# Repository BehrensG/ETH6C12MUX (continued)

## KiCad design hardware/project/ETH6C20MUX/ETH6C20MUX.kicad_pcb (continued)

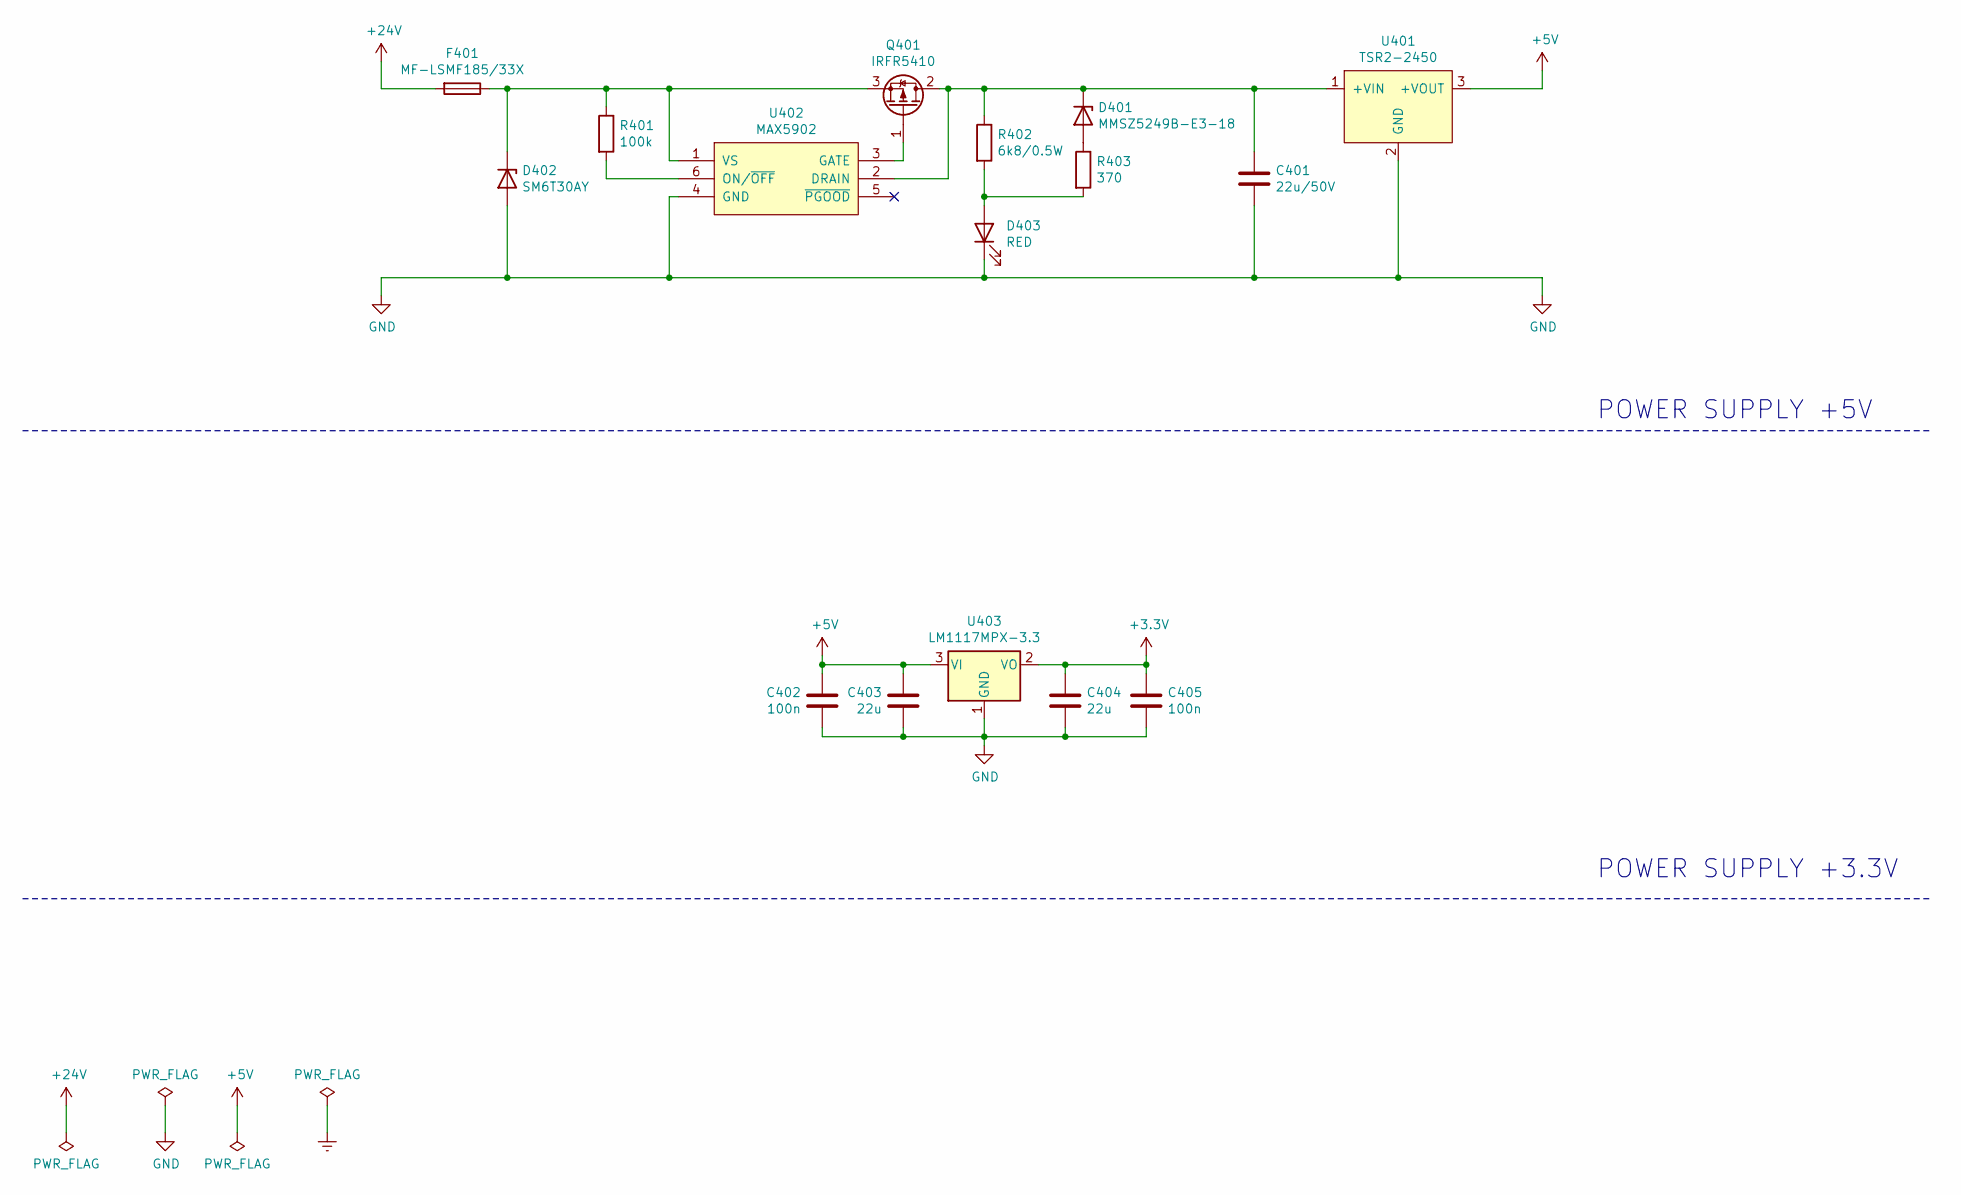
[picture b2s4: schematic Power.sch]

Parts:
C401: 22u/50V; C_2220_5650Metric_Pad1.97x5.40mm_HandSolder
C402, C405: 100n; C_0603_1608Metric_Pad1.08x0.95mm_HandSolder
C403, C404: 22u; C_1210_3225Metric_Pad1.42x2.65mm_HandSolder
D401: MMSZ5249B-E3-18; D_SOD-123
D402: SM6T30AY; DO_214AA_REV
D403: RED; LED_0603_1608Metric_Pad1.05x0.95mm_HandSolder
F401: MF-LSMF185/33X; Fuse_SMD2920
Q401: IRFR5410; TO-252-2_Rectifier
R401: 100k; R_0603_1608Metric_Pad0.98x0.95mm_HandSolder
R402: 6k8/0.5W; R_0603_1608Metric_Pad0.98x0.95mm_HandSolder
R403: 370; R_0603_1608Metric_Pad0.98x0.95mm_HandSolder
U401: TSR2-2450; TSR2
U402: MAX5902; SOT-23-6_Handsoldering
U403: LM1117MPX-3.3; SOT-223-3_TabPin2

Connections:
+3V3: C404.1, C405.1, U403.2 (VO); also elsewhere on the board
+5V: C402.1, C403.1, U401.3 (+VOUT), U403.3 (VI); also elsewhere on the board
+24V: F401.2; also elsewhere on the board
GND: C401.2, C402.2, C403.2, C404.2, C405.2, D402.2 (A), D403.1 (K), U401.2 (GND), U402.4 (GND), U403.1 (GND); also elsewhere on the board
unnamed: C401.1, D401.1 (K), Q401.2 (D), R402.1, U401.1 (+VIN), U402.2 (DRAIN)
unnamed: D401.2 (A), R403.1
unnamed: D402.1 (K), F401.1, Q401.3 (S), R401.1, U402.1 (VS)
unnamed: D403.2 (A), R402.2, R403.2
unnamed: Q401.1 (G), U402.3 (GATE)
unnamed: R401.2, U402.6 (ON/~OFF)

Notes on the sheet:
POWER SUPPLY +5V
POWER SUPPLY +3.3V

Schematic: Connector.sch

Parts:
F501, F502, F503, F504, F505, F506: 0470001.DRSNP; 0470
J501: Conn_01x06; PinSocket_1x06_P2.54mm_Vertical
J502: Conn_02x08_Odd_Even; PinSocket_2x08_P2.54mm_Vertical
J503: C64AC; Socket_DIN41612-CaseC1-AC-Male-64Pin-2rows

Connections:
+5V: J502.2, J502.4; also elsewhere on the board
+24V: J503.A31 (31A), J503.A32 (32A), J503.C31 (31C), J503.C32 (32C); also elsewhere on the board
/Connector/A: F501.2, J501.1, J501.2; also elsewhere on the board
/Connector/B: F502.2, J501.3, J501.4; also elsewhere on the board
/Connector/C: F503.2, J501.5, J501.6; also elsewhere on the board
/Connector/D: F504.2, J501.11, J501.12; also elsewhere on the board
/Connector/E: F505.2, J501.9, J501.10; also elsewhere on the board
/Connector/F: F506.2, J501.7, J501.8; also elsewhere on the board
/Connector/MODULE_DETECT0: J502.12; also elsewhere on the board
/Connector/MODULE_DETECT1: J502.14; also elsewhere on the board
/Connector/RELAY2_SCLK: J502.1; also elsewhere on the board
/Connector/RELAY2_SI: J502.5; also elsewhere on the board
/Connector/RELAY2_SO: J502.3; also elsewhere on the board
/Connector/RELAY2_~CS0: J502.9; also elsewhere on the board
/Connector/RELAY2_~CS1: J502.11; also elsewhere on the board
/Connector/RELAY2_~CS2: J502.13; also elsewhere on the board
/Connector/RELAY2_~CS3: J502.15; also elsewhere on the board
/Connector/RELAY2_~CS4: J502.16; also elsewhere on the board
/Connector/RELAY2_~RST: J502.7; also elsewhere on the board
/Connector/RX+: J503.A20 (20A); also elsewhere on the board
/Connector/RX-: J503.A21 (21A); also elsewhere on the board
/Connector/TX+: J503.C20 (20C); also elsewhere on the board
/Connector/TX-: J503.C21 (21C); also elsewhere on the board
Earth: J503.A18 (18A), J503.A22 (22A), J503.C18 (18C), J503.C22 (22C); also elsewhere on the board
GND: J502.6, J502.8, J503.A27 (27A), J503.A28 (28A), J503.C27 (27C), J503.C28 (28C); also elsewhere on the board
unnamed: F501.1, J503.A2 (2A), J503.C2 (2C)
unnamed: F502.1, J503.A3 (3A), J503.C3 (3C)
unnamed: F503.1, J503.A4 (4A), J503.C4 (4C)
unnamed: F504.1, J503.A5 (5A), J503.C5 (5C)
unnamed: F505.1, J503.A6 (6A), J503.C6 (6C)
unnamed: F506.1, J503.A7 (7A), J503.C7 (7C)

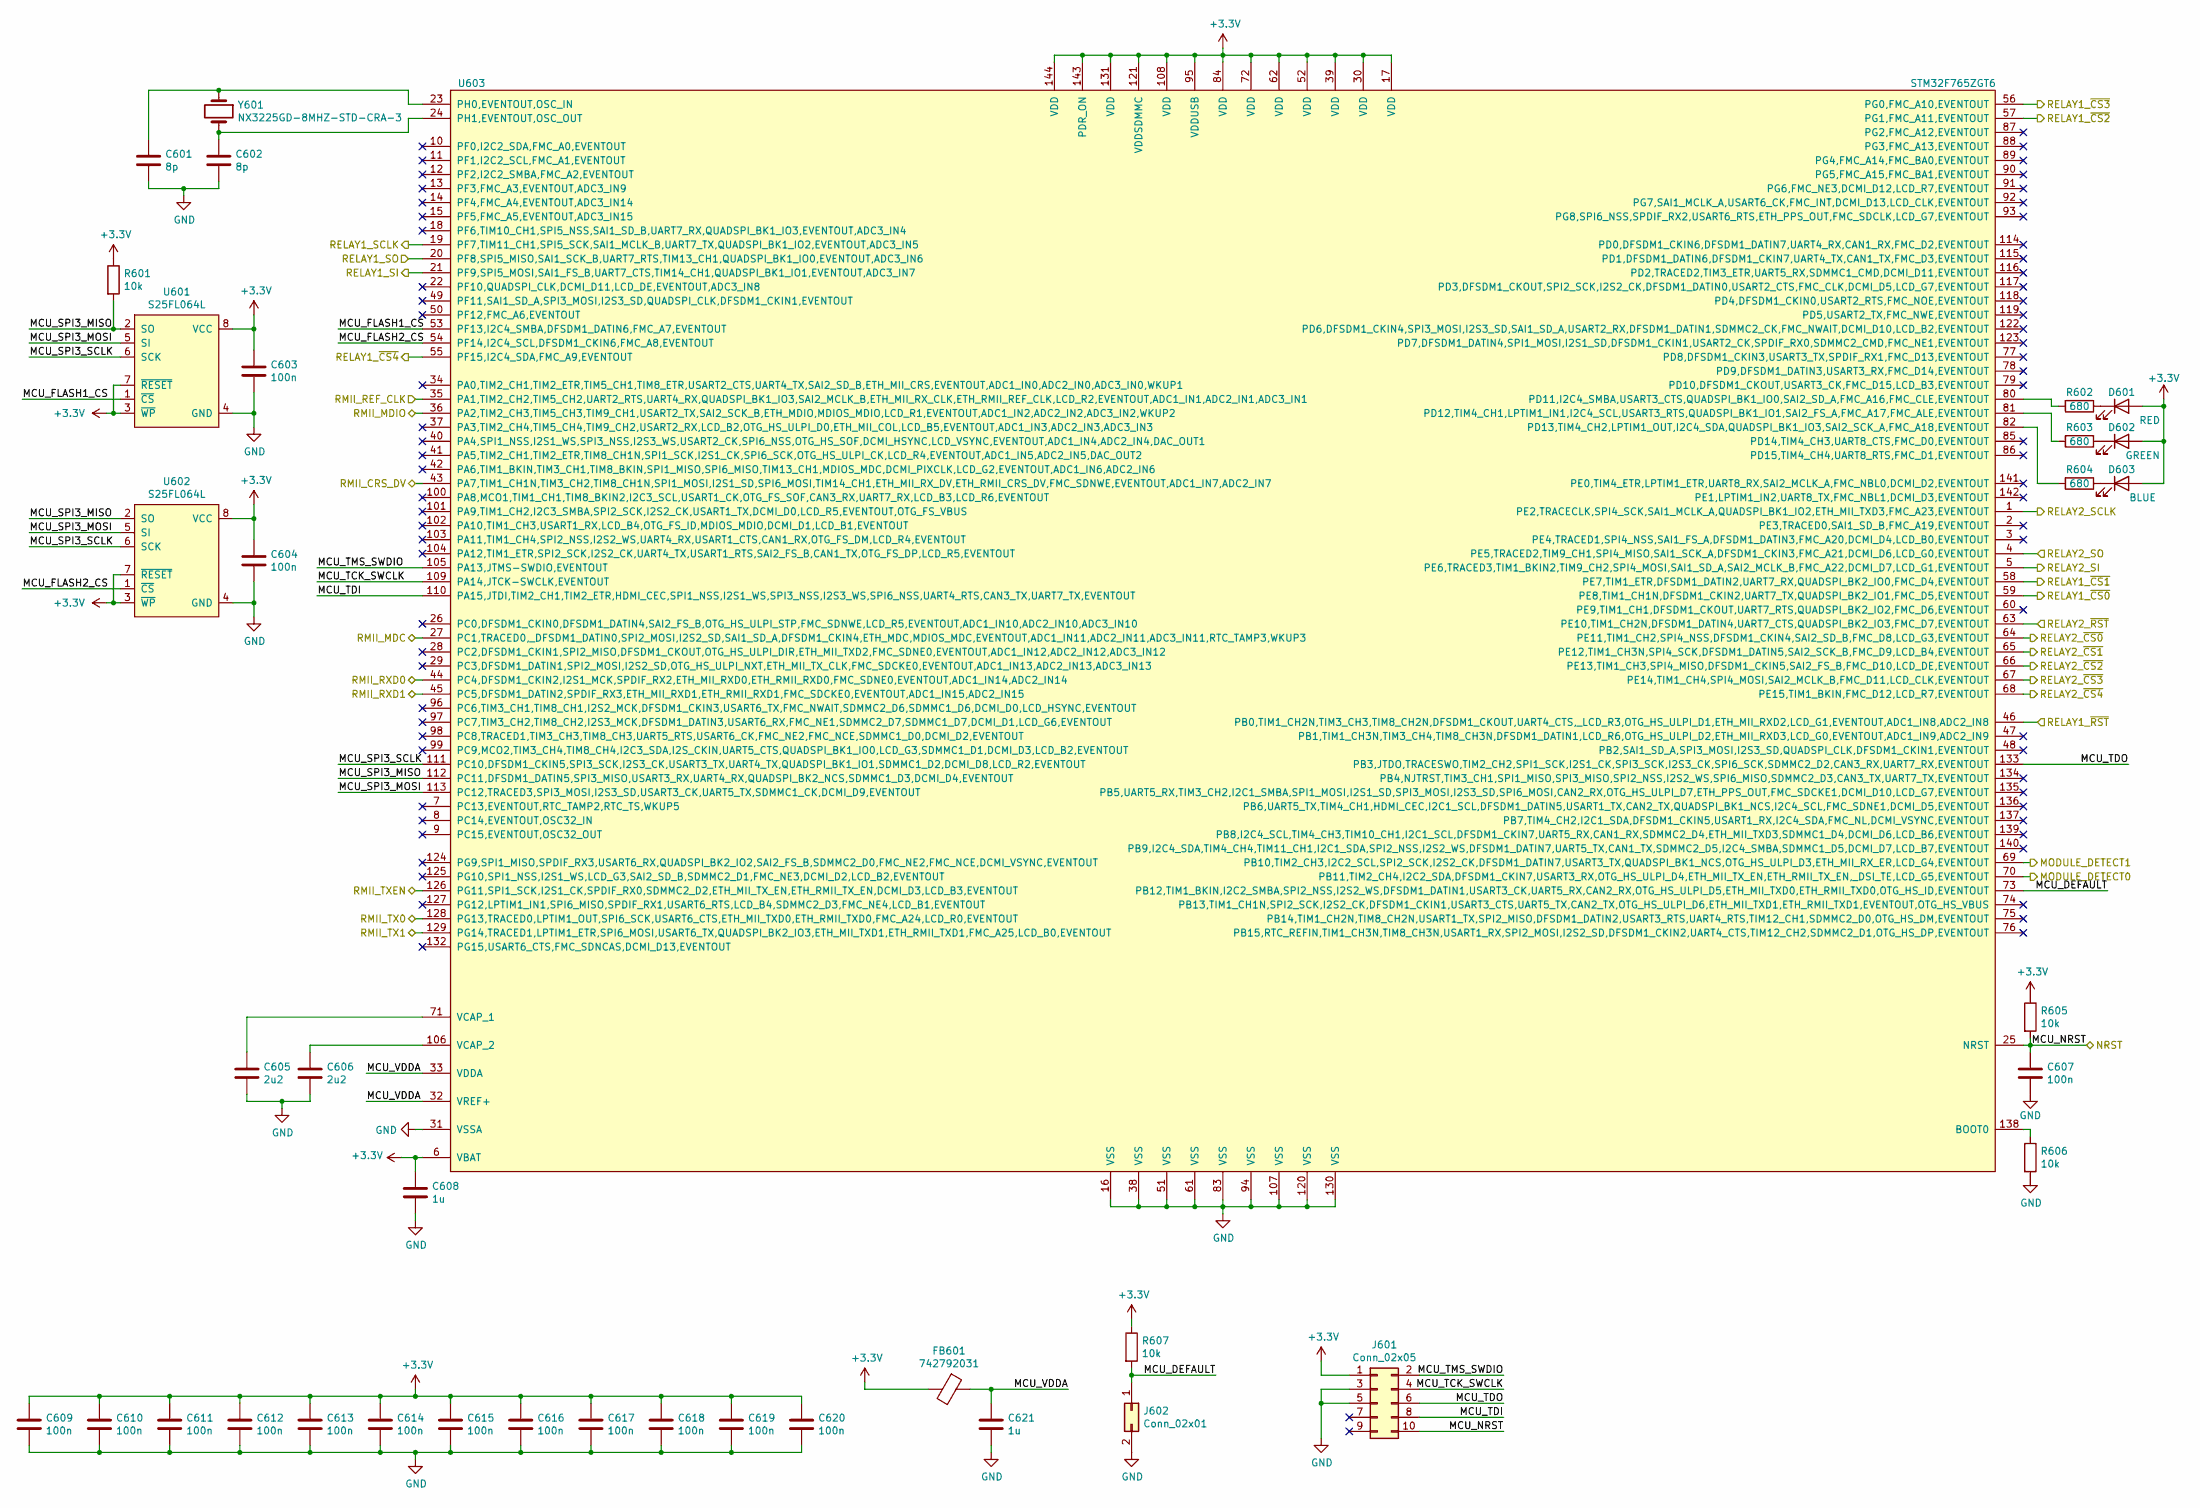
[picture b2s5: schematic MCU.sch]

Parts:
C601, C602: 8p; C_0603_1608Metric_Pad1.08x0.95mm_HandSolder
C603, C604, C607, C609, C610, C611, C612, C613, C614, C615, C616, C617, C618, C619, C620: 100n; C_0603_1608Metric_Pad1.08x0.95mm_HandSolder
C605, C606: 2u2; C_0805_2012Metric_Pad1.15x1.40mm_HandSolder
C608, C621: 1u; C_0603_1608Metric_Pad1.08x0.95mm_HandSolder
D601: RED; LED_Dialight_591
D602: GREEN; LED_Dialight_591
D603: BLUE; LED_Dialight_591
FB601: 742792031; R_0805_2012Metric_Pad1.15x1.40mm_HandSolder
J601: Conn_02x05; PinHeader_2x05_P1.27mm_Vertical
J602: Conn_02x01; PinHeader_1x02_P2.54mm_Vertical
R601, R605, R606, R607: 10k; R_0603_1608Metric_Pad0.98x0.95mm_HandSolder
R602, R603, R604: 680; R_0603_1608Metric_Pad0.98x0.95mm_HandSolder
U601, U602: S25FL064L; SOIC-8_5.23x5.23mm_P1.27mm
U603: STM32F765ZGT6; TQFP-144_20x20mm_P0.5mm
Y601: NX3225GD-8MHZ-STD-CRA-3; NX3225GD

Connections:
+3V3: C603.1, C604.1, C608.1, C609.1, C610.1, C611.1, C612.1, C613.1, C614.1, C615.1, C616.1, C617.1, C618.1, C619.1, C620.1, D601.2 (A), D602.2 (A), D603.2 (A), FB601.2, J601.1, R601.1, R605.1, R607.1, U601.3 (~WP), U601.7 (~RESET), U601.8 (VCC), U602.3 (~WP), U602.7 (~RESET), U602.8 (VCC), U603.6 (VBAT), U603.17 (VDD), U603.30 (VDD), U603.39 (VDD), U603.52 (VDD), U603.62 (VDD), U603.72 (VDD), U603.84 (VDD), U603.95 (VDDUSB), U603.108 (VDD), U603.121 (VDDSDMMC), U603.131 (VDD), U603.143 (PDR_ON), U603.144 (VDD); also elsewhere on the board
/Connector/MODULE_DETECT0: U603.70 (PB11,TIM2_CH4,I2C2_SDA,DFSDM1_CKIN7,USA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); also elsewhere on the board
/Connector/MODULE_DETECT1: U603.69 (PB10,TIM2_CH3,I2C2_SCL,SPI2_SCK,I2S2_CK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); also elsewhere on the board
/Connector/RELAY2_SCLK: U603.1 (PE2,TRACECLK,SPI4_SCK,SAI1_MCLK_A,QUADS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); also elsewhere on the board
/Connector/RELAY2_SI: U603.5 (PE6,TRACED3,TIM1_BKIN2,TIM9_CH2,SPI4_MO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); also elsewhere on the board
/Connector/RELAY2_SO: U603.4 (PE5,TRACED2,TIM9_CH1,SPI4_MISO,SAI1_SCK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); also elsewhere on the board
/Connector/RELAY2_~CS0: U603.64 (PE11,TIM1_CH2,SPI4_NSS,DFSDM1_CKIN4,SAI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); also elsewhere on the board
/Connector/RELAY2_~CS1: U603.65 (PE12,TIM1_CH3N,SPI4_SCK,DFSDM1_DATIN5,S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); also elsewhere on the board
/Connector/RELAY2_~CS2: U603.66 (PE13,TIM1_CH3,SPI4_MISO,DFSDM1_CKIN5,SA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); also elsewhere on the board
/Connector/RELAY2_~CS3: U603.67 (PE14,TIM1_CH4,SPI4_MOSI,SAI2_MCLK_B,FMC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); also elsewhere on the board
/Connector/RELAY2_~CS4: U603.68 (PE15,TIM1_BKIN,FMC_D12,LCD_R7,EVENTOUT); also elsewhere on the board
/Connector/RELAY2_~RST: U603.63 (PE10,TIM1_CH2N,DFSDM1_DATIN4,UART7_CTS,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); also elsewhere on the board
/Ethernet/NRST: C607.1, J601.10, R605.2, U603.25 (NRST); also elsewhere on the board
/Ethernet/REF_CLK: U603.35 (PA1,TIM2_CH2,TIM5_CH2,UART2_RTS,UART4_R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); also elsewhere on the board
/Ethernet/RMII_CRS_DV: U603.43 (PA7,TIM1_CH1N,TIM3_CH2,TIM8_CH1N,SPI1_M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); also elsewhere on the board
/Ethernet/RMII_MDC: U603.27 (PC1,TRACED0,_DFSDM1_DATIN0,SPI2_MOSI,I2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); also elsewhere on the board
/Ethernet/RMII_MDIO: U603.36 (PA2,TIM2_CH3,TIM5_CH3,TIM9_CH1,USART2_T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); also elsewhere on the board
/Ethernet/RMII_RXD0: U603.44 (PC4,DFSDM1_CKIN2,I2S1_MCK,SPDIF_RX2,ETH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); also elsewhere on the board
/Ethernet/RMII_RXD1: U603.45 (PC5,DFSDM1_DATIN2,SPDIF_RX3,ETH_MII_RXD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); also elsewhere on the board
/Ethernet/RMII_TXEN: U603.126 (PG11,SPI1_SCK,I2S1_CK,SPDIF_RX0,SDMMC2_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); also elsewhere on the board
/MCU/MCU_DEFAULT: J602.1, R607.2, U603.73 (PB12,TIM1_BKIN,I2C2_SMBA,SPI2_NSS,I2S2_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)
/MCU/MCU_FLASH1_CS: U601.1 (~CS), U603.53 (PF13,I2C4_SMBA,DFSDM1_DATIN6,FMC_A7,EVE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)
/MCU/MCU_FLASH2_CS: U602.1 (~CS), U603.54 (PF14,I2C4_SCL,DFSDM1_CKIN6,FMC_A8,EVENT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)
/MCU/MCU_SPI3_MISO: R601.2, U601.2 (SO), U602.2 (SO), U603.112 (PC11,DFSDM1_DATIN5,SPI3_MISO,USART3_RX,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)
/MCU/MCU_SPI3_MOSI: U601.5 (SI), U602.5 (SI), U603.113 (PC12,TRACED3,SPI3_MOSI,I2S3_SD,USART3_C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)
/MCU/MCU_SPI3_SCLK: U601.6 (SCK), U602.6 (SCK), U603.111 (PC10,DFSDM1_CKIN5,SPI3_SCK,I2S3_CK,USAR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)
/MCU/MCU_TCK_SWCLK: J601.4, U603.109 (PA14,JTCK-SWCLK,EVENTOUT)
/MCU/MCU_TDI: J601.8, U603.110 (PA15,JTDI,TIM2_CH1,TIM2_ETR,HDMI_CEC,SP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)
/MCU/MCU_TDO: J601.6, U603.133 (PB3,JTDO,TRACESWO,TIM2_CH2,SPI1_SCK,I2S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)
/MCU/MCU_TMS_SWDIO: J601.2, U603.105 (PA13,JTMS-SWDIO,EVENTOUT)
/MCU/MCU_VDDA: C621.1, FB601.1, U603.32 (VREF+), U603.33 (VDDA)
/MCU/RELAY1_SCLK: U603.19 (PF7,TIM11_CH1,SPI5_SCK,SAI1_MCLK_B,UART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); also elsewhere on the board
/MCU/RELAY1_SI: U603.21 (PF9,SPI5_MOSI,SAI1_FS_B,UART7_CTS,TIM14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); also elsewhere on the board
/MCU/RELAY1_SO: U603.20 (PF8,SPI5_MISO,SAI1_SCK_B,UART7_RTS,TIM1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); also elsewhere on the board
/MCU/RELAY1_~CS0: U603.59 (PE8,TIM1_CH1N,DFSDM1_CKIN2,UART7_TX,QUA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); also elsewhere on the board
/MCU/RELAY1_~CS1: U603.58 (PE7,TIM1_ETR,DFSDM1_DATIN2,UART7_RX,QUA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); also elsewhere on the board
/MCU/RELAY1_~CS2: U603.57 (PG1,FMC_A11,EVENTOUT); also elsewhere on the board
/MCU/RELAY1_~CS3: U603.56 (PG0,FMC_A10,EVENTOUT); also elsewhere on the board
/MCU/RELAY1_~CS4: U603.55 (PF15,I2C4_SDA,FMC_A9,EVENTOUT); also elsewhere on the board
/MCU/RELAY1_~RST: U603.46 (PB0,TIM1_CH2N,TIM3_CH3,TIM8_CH2N,DFSDM1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); also elsewhere on the board
/MCU/RMII_TX0: U603.128 (PG13,TRACED0,LPTIM1_OUT,SPI6_SCK,USART6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); also elsewhere on the board
/MCU/RMII_TX1: U603.129 (PG14,TRACED1,LPTIM1_ETR,SPI6_MOSI,USART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); also elsewhere on the board
GND: C601.2, C602.2, C603.2, C604.2, C605.2, C606.2, C607.2, C608.2, C609.2, C610.2, C611.2, C612.2, C613.2, C614.2, C615.2, C616.2, C617.2, C618.2, C619.2, C620.2, C621.2, J601.3, J601.5, J602.2, R606.2, U601.4 (GND), U602.4 (GND), U603.16 (VSS), U603.31 (VSSA), U603.38 (VSS), U603.51 (VSS), U603.61 (VSS), U603.83 (VSS), U603.94 (VSS), U603.107 (VSS), U603.120 (VSS), U603.130 (VSS); also elsewhere on the board
unnamed: C601.1, U603.23 (PH0,EVENTOUT,OSC_IN), Y601.1
unnamed: C602.1, U603.24 (PH1,EVENTOUT,OSC_OUT), Y601.2
unnamed: C605.1, U603.71 (VCAP_1)
unnamed: C606.1, U603.106 (VCAP_2)
unnamed: D601.1 (K), R602.1
unnamed: D602.1 (K), R603.1
unnamed: D603.1 (K), R604.1
unnamed: R602.2, U603.80 (PD11,I2C4_SMBA,USART3_CTS,QUADSPI_BK1_I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)
unnamed: R603.2, U603.81 (PD12,TIM4_CH1,LPTIM1_IN1,I2C4_SCL,USART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)
unnamed: R604.2, U603.82 (PD13,TIM4_CH2,LPTIM1_OUT,I2C4_SDA,QUADS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)
unnamed: R606.1, U603.138 (BOOT0)

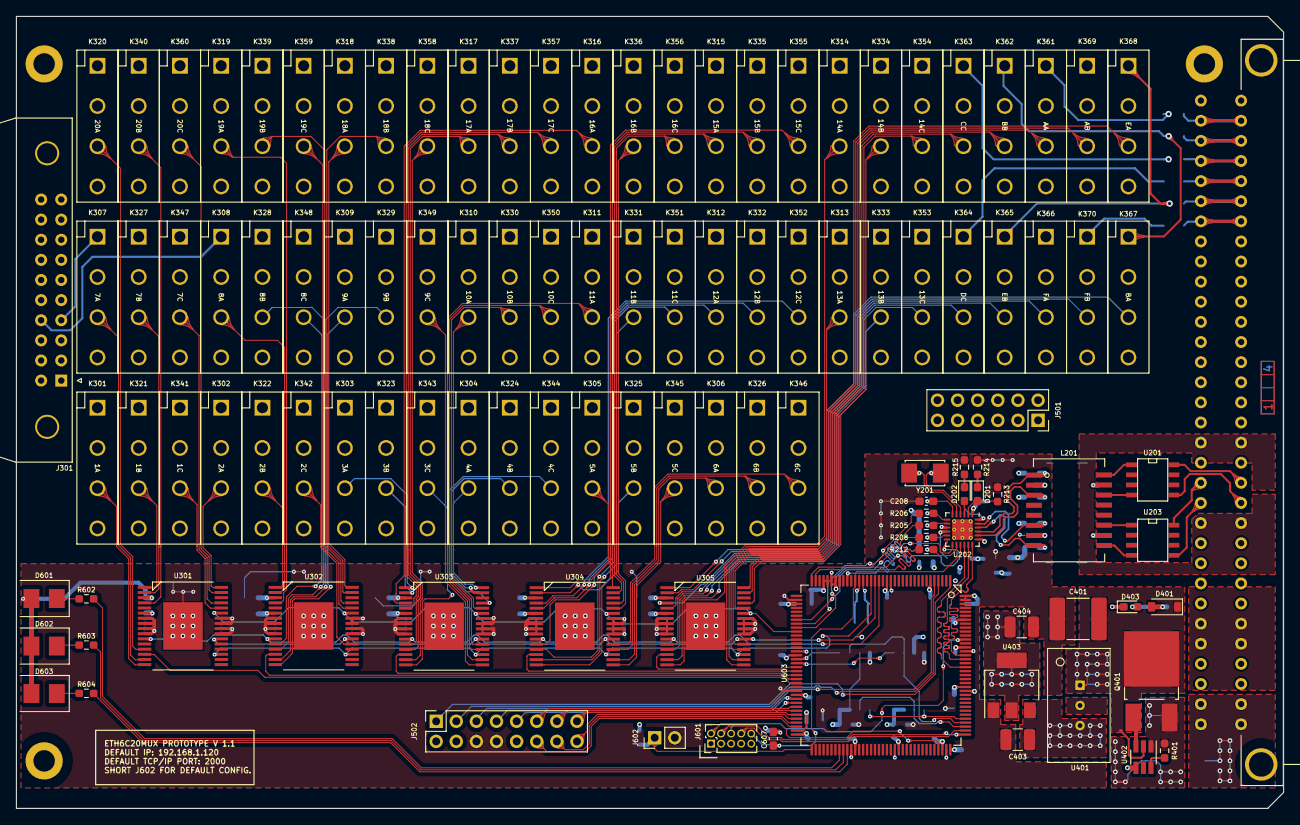
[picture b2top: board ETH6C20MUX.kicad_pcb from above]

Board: 4 copper layers, 160.0 x 100.0 mm, 195 parts (0 on the bottom side), 197 nets.

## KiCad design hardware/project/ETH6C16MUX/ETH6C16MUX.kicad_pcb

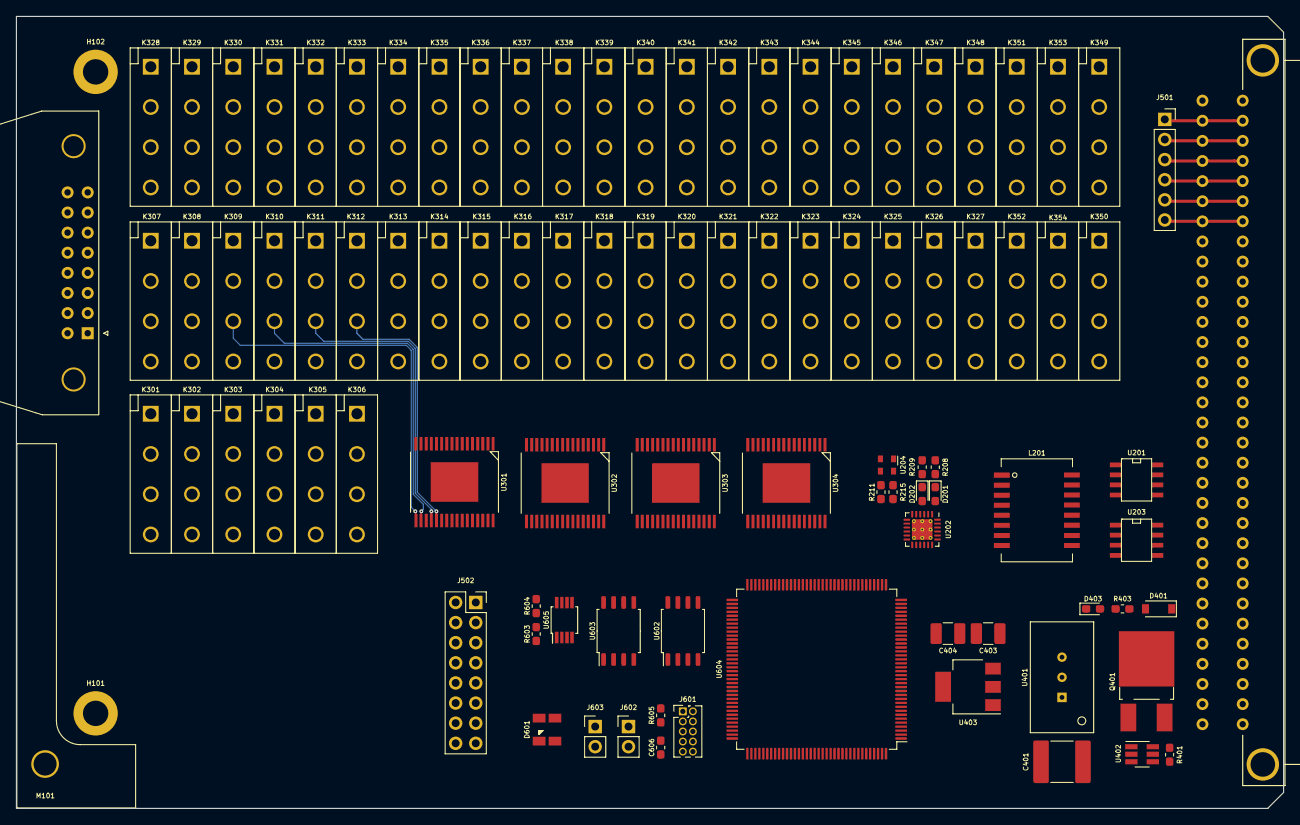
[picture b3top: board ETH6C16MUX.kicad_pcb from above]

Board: 4 copper layers, 160.0 x 100.0 mm, 159 parts (0 on the bottom side), 170 nets.

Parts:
C201, C202, C204, C205, C206, C207, C210, C213, C402, C405, C601, C602, C603, C606, C608, C609, C610, C611, C612, C613, C614, C615, C616, C617, C618, C619: 100n; C_0603_1608Metric_Pad1.05x0.95mm_HandSolder
C203, C209, C607, C620: 1u; C_0603_1608Metric_Pad1.05x0.95mm_HandSolder
C208: 470p; C_0603_1608Metric_Pad1.05x0.95mm_HandSolder
C211, C212: 1n/1kV; C_1206_3216Metric_Pad1.42x1.75mm_HandSolder
C401: 22u/50V; C_2220_5650Metric_Pad1.97x5.40mm_HandSolder
C403, C404: 22u; C_1210_3225Metric_Pad1.42x2.65mm_HandSolder
C604, C605: 2u2; C_0805_2012Metric_Pad1.15x1.40mm_HandSolder
D201: YELLOW; LED_0603_1608Metric_Pad1.05x0.95mm_HandSolder
D202: GREEN; LED_0603_1608Metric_Pad1.05x0.95mm_HandSolder
D401: MMSZ5249B-E3-18; D_SOD-123
D402: SM6T30AY; DO_214AA_REV
D403: RED; LED_0603_1608Metric_Pad1.05x0.95mm_HandSolder
D601: 150121M153000
F401: MF-LSMF185/33X; Fuse_SMD2920
FB201, FB601: 742792031; R_0805_2012Metric_Pad1.15x1.40mm_HandSolder
H101, H102: MountingHole; MountingHole_3.2mm_M3_DIN965_Pad
J301: Conn_02x08_Counter_Clockwise; IDC-Header_2x08_P2.54mm_Horizontal_Lock
J501: Conn_01x06; PinSocket_1x06_P2.54mm_Vertical
J502: Conn_02x08_Odd_Even; PinSocket_2x08_P2.54mm_Vertical
J503: C64AC; Socket_DIN41612-CaseC1-AC-Male-64Pin-2rows
J601: Conn_02x05; PinHeader_2x05_P1.27mm_Vertical
J602, J603: Conn_02x01; PinHeader_1x02_P2.54mm_Vertical
K301, K302, K303, K304, K305, K306, K307, K308, K309, K310, K311, K312, K313, K314, K315, K316, K317, K318, K319, K320, K321, K322, K323, K324, K325, K326, K327, K328, K329, K330, K331, K332, K333, K334, K335, K336, K337, K338, K339, K340, K341, K342, K343, K344, K345, K346, K347, K348, K349, K350, K351, K352, K353, K354: HE3621A0500; HE360_x-5331272-5
L201: 749010012A
M101: 60817-096
Q401: IRFR5410; TO-252-2_Rectifier
R201, R202, R203, R204: 49R9; R_0603_1608Metric_Pad1.05x0.95mm_HandSolder
R205: 12k1; R_0603_1608Metric_Pad1.05x0.95mm_HandSolder
R206, R207: 75/1%; R_0603_1608Metric_Pad1.05x0.95mm_HandSolder
R208, R209: 270; R_0603_1608Metric_Pad1.05x0.95mm_HandSolder
R210: 1M/1kV; R_1206_3216Metric_Pad1.42x1.75mm_HandSolder
R211, R215, R601: 220; R_0603_1608Metric_Pad1.05x0.95mm_HandSolder
R212, R213, R214, R602, R605, R611, R612: 10k; R_0603_1608Metric_Pad1.05x0.95mm_HandSolder
R401: 100k; R_0603_1608Metric_Pad1.05x0.95mm_HandSolder
R402: 6k8/0.5W; R_0805_2012Metric_Pad1.15x1.40mm_HandSolder
R403: 370; R_0603_1608Metric_Pad1.05x0.95mm_HandSolder
R603, R604: 4k7; R_0603_1608Metric_Pad1.05x0.95mm_HandSolder
R606: 523; R_0603_1608Metric_Pad1.05x0.95mm_HandSolder
R607, R608: 330; R_0603_1608Metric_Pad1.05x0.95mm_HandSolder
R609: 0; R_0603_1608Metric_Pad1.05x0.95mm_HandSolder
R610: R; R_0603_1608Metric_Pad1.05x0.95mm_HandSolder
U201, U203: LC03-3.3; SO8E
U202: LAN8742; QFN-24-1EP_4x4mm_P0.5mm_EP2.6x2.6mm_ThermalVias
U204: ASDM1-50.000MHZ-LC-T; Oscillator_SMD_Abracon_ASDMB-4Pin_2.5x2.0mm
U301, U302, U303, U304: MCZ33996; HSOP-32-1EP_7.5x11.0mm_P0.65mm_ThermalVias
U401: TSR2-2450; TSR2
U402: MAX5902; SOT-23-6_Handsoldering
U403: LM1117MPX-3.3; SOT-223-3_TabPin2
U601: ASDM1-20.000MHZ-LC-T; Oscillator_SMD_Abracon_ASDMB-4Pin_2.5x2.0mm
U602, U603: S25FL064L_SOIC; SOIC-8_5.23x5.23mm_P1.27mm
U604: STM32F765ZGT6; TQFP-144_20x20mm_P0.5mm
U605: MCP9804; MSOP-8_3x3mm_P0.65mm

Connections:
+3V3: C201.1, C202.1, C213.1, C404.1, C405.1, C601.1, C602.1, C603.1, C608.1, C609.1, C610.1, C611.1, C612.1, C613.1, C614.1, C615.1, C616.1, C617.1, C618.1, C619.1, D601.1, FB201.2, FB601.2, J601.1, R212.1, R213.1, R214.1, R602.1, R603.1, R604.1, R605.1, R609.2, R611.1, R612.1, U202.9, U204.1, U204.4, U301.3, U302.3, U303.3, U304.3, U403.2, U601.1, U601.4, U602.3, U602.7, U602.8, U603.3, U603.7, U603.8, U604.17, U604.30, U604.39, U604.52, U604.62, U604.72, U604.84, U604.95, U604.108, U604.121, U604.131, U604.143, U604.144, U605.5, U605.6, U605.7, U605.8
+5V: C402.1, C403.1, J502.2, J502.4, J502.6, K301.2, K302.2, K303.2, K304.2, K305.2, K306.2, K307.2, K308.2, K309.2, K310.2, K311.2, K312.2, K313.2, K314.2, K315.2, K316.2, K317.2, K318.2, K319.2, K320.2, K321.2, K322.2, K323.2, K324.2, K325.2, K326.2, K327.2, K328.2, K329.2, K330.2, K331.2, K332.2, K333.2, K334.2, K335.2, K336.2, K337.2, K338.2, K339.2, K340.2, K341.2, K342.2, K343.2, K344.2, K345.2, K346.2, K347.2, K348.2, K349.2, K350.2, K351.2, K352.2, K353.2, K354.2, U301.6, U302.6, U303.6, U304.6, U401.3, U403.3
+24V: F401.2, J503.A31, J503.A32, J503.C31, J503.C32
/Connector/A: J501.1, J503.A2, J503.C2, K349.1
/Connector/B: J501.2, J503.A3, J503.C3, K353.1
/Connector/C: J501.3, J503.A4, J503.C4, K351.1
/Connector/D: J501.4, J503.A5, J503.C5, K352.1
/Connector/E: J501.5, J503.A6, J503.C6, K354.1
/Connector/F: J501.6, J503.A7, J503.C7, K350.1
/Connector/MODULE_DETECT0: J502.14, U604.46
/Connector/MODULE_DETECT1: J502.16, U604.47
/Connector/RELAY2_SCLK: J502.1, U604.1
/Connector/RELAY2_SI: J502.5, U604.5
/Connector/RELAY2_SO: J502.3, U604.4
/Connector/RELAY2_~CS0: J502.9, U604.7
/Connector/RELAY2_~CS1: J502.11, U604.8
/Connector/RELAY2_~CS2: J502.13, U604.9
/Connector/RELAY2_~CS3: J502.15, U604.10
/Connector/RELAY2_~RST: J502.7, U604.2
/Connector/RX+: J503.A20, U203.8
/Connector/RX-: J503.A21, U203.5
/Connector/TX+: J503.C20, U201.8
/Connector/TX-: J503.C21, U201.5
/Ethernet/ETH_REFCLK_PHY_50MHZ: R215.1, U202.5
/Ethernet/ETH_RMII_CRS_DV: U202.11, U604.43
/Ethernet/ETH_RMII_MDC: U202.13, U604.27
/Ethernet/ETH_RMII_MDIO: R213.2, U202.12, U604.36
/Ethernet/ETH_RMII_REF_CLK: R211.1, U604.35
/Ethernet/ETH_RMII_RX0: U202.8, U604.44
/Ethernet/ETH_RMII_RX1: U202.7, U604.45
/Ethernet/ETH_RMII_TX0: U202.17, U604.128
/Ethernet/ETH_RMII_TX1: U202.18, U604.129
/Ethernet/ETH_RMII_TXEN: U202.16, U604.126
/Ethernet/ETH_RXER: R212.2, U202.10
/Ethernet/ETH_RXN: L201.8, R204.2, U202.22
/Ethernet/ETH_RXP: L201.6, R203.2, U202.23
/Ethernet/ETH_TXN: L201.3, R202.2, U202.20
/Ethernet/ETH_TXP: L201.1, R201.2, U202.21
/Ethernet/ETH_~INT: R214.2, U202.14, U604.37
/Ethernet/ETH_~RST: C606.1, J601.10, R605.2, U202.15, U604.25
/MCU/I2C_SCL: R604.2, U604.54, U605.2
/MCU/I2C_SDA: R603.2, U604.55, U605.1
/MCU/LED_BLUE: R608.2, U604.103
/MCU/LED_GREEN: R607.2, U604.102
/MCU/LED_RED: R606.2, U604.101
/MCU/MCU_BOOT: J602.1, R611.2, U604.104
/MCU/MCU_DEFAULT: J603.1, R612.2, U604.142
/MCU/MCU_FLASH1_CS: U602.1, U604.98
/MCU/MCU_FLASH2_CS: U603.1, U604.99
/MCU/MCU_SPI3_MISO: R602.2, U602.2, U603.2, U604.112
/MCU/MCU_SPI3_MOSI: U602.5, U603.5, U604.113
/MCU/MCU_SPI3_SCLK: U602.6, U603.6, U604.111
/MCU/MCU_TCK_SWCLK: J601.4, U604.109
/MCU/MCU_TDI: J601.8, U604.110
/MCU/MCU_TDO: J601.6, U604.133
/MCU/MCU_TMS_SWDIO: J601.2, U604.105
/MCU/MCU_VDDA: C620.1, FB601.1, U604.32, U604.33
/MCU/RELAY1_SCLK: U301.11, U302.11, U303.11, U304.11, U604.19
/MCU/RELAY1_SI: U301.19, U302.19, U303.19, U304.19, U604.21
/MCU/RELAY1_SO: U301.22, U302.22, U303.22, U304.22, U604.20
/MCU/RELAY1_~CS0: U301.14, U604.22
/MCU/RELAY1_~CS1: U303.14, U604.49
/MCU/RELAY1_~CS2: U302.14, U604.50
/MCU/RELAY1_~CS3: U304.14, U604.53
/MCU/RELAY1_~RST: U301.27, U302.27, U303.27, U304.27, U604.15
/Relays/PIN1: J301.1, K301.1, K302.1, K303.1
/Relays/PIN2: J301.2, K304.1, K305.1, K306.1
/Relays/PIN3: J301.3, K307.1, K308.1, K309.1
/Relays/PIN4: J301.4, K310.1, K311.1, K312.1
/Relays/PIN5: J301.5, K313.1, K314.1, K315.1
/Relays/PIN6: J301.6, K316.1, K317.1, K318.1
/Relays/PIN7: J301.7, K319.1, K320.1, K321.1
/Relays/PIN8: J301.8, K322.1, K323.1, K324.1
/Relays/PIN9: J301.9, K325.1, K326.1, K327.1
/Relays/PIN10: J301.10, K328.1, K329.1, K330.1
/Relays/PIN10A: K301.4, K304.4, K307.4, K310.4, K313.4, K316.4, K319.4, K322.4, K325.4, K328.4, K331.4, K334.4, K337.4, K340.4, K343.4, K346.4, K349.4, K350.4
/Relays/PIN10B: K302.4, K305.4, K308.4, K311.4, K314.4, K317.4, K320.4, K323.4, K326.4, K329.4, K332.4, K335.4, K338.4, K341.4, K344.4, K347.4, K353.4, K354.4
/Relays/PIN10C: K303.4, K306.4, K309.4, K312.4, K315.4, K318.4, K321.4, K324.4, K327.4, K330.4, K333.4, K336.4, K339.4, K342.4, K345.4, K348.4, K351.4, K352.4
/Relays/PIN11: J301.11, K331.1, K332.1, K333.1
/Relays/PIN12: J301.12, K334.1, K335.1, K336.1
/Relays/PIN13: J301.13, K337.1, K338.1, K339.1
/Relays/PIN14: J301.14, K340.1, K341.1, K342.1
/Relays/PIN15: J301.15, K343.1, K344.1, K345.1
/Relays/PIN16: J301.16, K346.1, K347.1, K348.1
/Relays/RELAY1A: K301.3, U301.1
/Relays/RELAY1B: K317.3, U303.1
/Relays/RELAY1C: K333.3, U302.1
/Relays/RELAY2A: K302.3, U301.2
/Relays/RELAY2B: K318.3, U303.2
/Relays/RELAY2C: K334.3, U302.2
/Relays/RELAY3A: K303.3, U301.4
/Relays/RELAY3B: K319.3, U303.4
/Relays/RELAY3C: K335.3, U302.4
/Relays/RELAY4A: K304.3, U301.5
/Relays/RELAY4B: K320.3, U303.5
/Relays/RELAY4C: K336.3, U302.5
/Relays/RELAY5A: K305.3, U301.12
/Relays/RELAY5B: K321.3, U303.12
/Relays/RELAY5C: K337.3, U302.12
/Relays/RELAY6A: K306.3, U301.13
/Relays/RELAY6B: K322.3, U303.13
/Relays/RELAY6C: K338.3, U302.13
/Relays/RELAY7A: K307.3, U301.15
/Relays/RELAY7B: K323.3, U303.15
/Relays/RELAY7C: K339.3, U302.15
/Relays/RELAY8A: K308.3, U301.16
/Relays/RELAY8B: K324.3, U303.16
/Relays/RELAY8C: K340.3, U302.16
/Relays/RELAY9A: K309.3, U301.17
/Relays/RELAY9B: K325.3, U303.17
/Relays/RELAY9C: K341.3, U302.17
/Relays/RELAY10A: K310.3, U301.18
/Relays/RELAY10B: K326.3, U303.18
/Relays/RELAY10C: K342.3, U302.18
/Relays/RELAY11A: K311.3, U301.20
/Relays/RELAY11B: K327.3, U303.20
/Relays/RELAY11C: K343.3, U302.20
/Relays/RELAY12A: K312.3, U301.21
/Relays/RELAY12B: K328.3, U303.21
/Relays/RELAY12C: K344.3, U302.21
/Relays/RELAY13A: K313.3, U301.28
/Relays/RELAY13B: K329.3, U303.28
/Relays/RELAY13C: K345.3, U302.28
/Relays/RELAY14A: K314.3, U301.29
/Relays/RELAY14B: K330.3, U303.29
/Relays/RELAY14C: K346.3, U302.29
/Relays/RELAY15A: K315.3, U301.31
/Relays/RELAY15B: K331.3, U303.31
/Relays/RELAY15C: K347.3, U302.31
/Relays/RELAY16A: K316.3, U301.32
/Relays/RELAY16B: K332.3, U303.32
/Relays/RELAY16C: K348.3, U302.32
/Relays/RELAYA: K349.3, U304.1
/Relays/RELAYB: K350.3, U304.2
/Relays/RELAYC: K351.3, U304.4
/Relays/RELAYD: K352.3, U304.5
/Relays/RELAYE: K353.3, U304.12
/Relays/RELAYF: K354.3, U304.13
Earth: C211.2, C212.1, J503.A18, J503.A22, J503.C18, J503.C22, R210.1
GND: C201.2, C202.2, C203.2, C204.2, C205.2, C206.2, C207.2, C208.2, C209.2, C210.2, C212.2, C213.2, C401.2, C402.2, C403.2, C404.2, C405.2, C601.2, C602.2, C603.2, C604.2, C605.2, C606.2, C607.2, C608.2, C609.2, C610.2, C611.2, C612.2, C613.2, C614.2, C615.2, C616.2, C617.2, C618.2, C619.2, C620.2, D402.2, D403.1, J502.8, J502.10, J502.12, J503.A27, J503.A28, J503.C27, J503.C28, J601.3, J601.5, J602.2, J603.2, R205.1, R208.2, R209.2, R210.2, R610.2, U202.25, U204.2, U301.7, U301.8, U301.9, U301.10, U301.23, U301.24, U301.25, U301.26, U301.33, U302.7, U302.8, U302.9, U302.10, U302.23, U302.24, U302.25, U302.26, U302.33, U303.7, U303.8, U303.9, U303.10, U303.23, U303.24, U303.25, U303.26, U303.33, U304.7, U304.8, U304.9, U304.10, U304.23, U304.24, U304.25, U304.26, U304.33, U401.2, U402.4, U403.1, U601.2, U602.4, U603.4, U604.16, U604.31, U604.38, U604.51, U604.61, U604.83, U604.94, U604.107, U604.120, U604.130, U605.4
unnamed: C203.1, C204.1, C205.1, C206.1, C207.1, C210.1, FB201.1, L201.2, L201.7, R201.1, R202.1, R203.1, R204.1, U202.1, U202.19
unnamed: C208.1, C209.1, U202.6
unnamed: C211.1, R206.2, R207.2
unnamed: C401.1, D401.1, Q401.2, R402.1, U401.1, U402.2
unnamed: C604.1, U604.71
unnamed: C605.1, U604.106
unnamed: C607.1, R609.1, U604.6
unnamed: D201.1, R208.1
unnamed: D201.2, U202.2
unnamed: D202.1, R209.1
unnamed: D202.2, U202.3
unnamed: D401.2, R403.1
unnamed: D402.1, F401.1, Q401.3, R401.1, U402.1
unnamed: D403.2, R402.2, R403.2
unnamed: D601.2, R606.1
unnamed: D601.3, R607.1
unnamed: D601.4, R608.1
unnamed: L201.9, U203.4
unnamed: L201.10, R206.1
unnamed: L201.11, U203.1
unnamed: L201.14, U201.4
unnamed: L201.15, R207.1
unnamed: L201.16, U201.1
unnamed: Q401.1, U402.3
unnamed: R205.2, U202.24
unnamed: R211.2, R215.2, U204.3
unnamed: R401.2, U402.6
unnamed: R601.1, U604.23
unnamed: R601.2, U601.3
unnamed: R610.1, U604.138

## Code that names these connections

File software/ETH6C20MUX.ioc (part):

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Mcu.Name=STM32F765Z(G-I)Tx
Mcu.Package=LQFP144
Mcu.UserName=STM32F765ZGTx
PA1.Mode=RMII
PA1.Signal=ETH_REF_CLK
PA13.Mode=Serial_Wire
PA13.Signal=SYS_JTMS-SWDIO
PA14.Mode=Serial_Wire
PA14.Signal=SYS_JTCK-SWCLK
PA2.Mode=RMII
PA2.Signal=ETH_MDIO
PA7.Mode=RMII
PA7.Signal=ETH_CRS_DV
PB0.GPIOParameters=GPIO_Speed,PinState,GPIO_PuPd,GPIO_Label
PB0.GPIO_Label=RELAY1_nRST
PB0.GPIO_PuPd=GPIO_PULLUP
PB0.GPIO_Speed=GPIO_SPEED_FREQ_VERY_HIGH
PB0.PinState=GPIO_PIN_SET
PB0.Signal=GPIO_Output
PB10.GPIOParameters=GPIO_PuPd,GPIO_Label
PB10.GPIO_Label=MODULE_DETECT1
PB10.GPIO_PuPd=GPIO_PULLDOWN
PB10.Signal=GPIO_Input
PB11.GPIOParameters=GPIO_PuPd,GPIO_Label
PB11.GPIO_Label=MODULE_DETECT0
PB11.GPIO_PuPd=GPIO_PULLDOWN
PB11.Signal=GPIO_Input
PB12.GPIOParameters=GPIO_Label
PB12.GPIO_Label=MCU_DEFAULT
PB12.Signal=GPIO_Input
PB13.GPIOParameters=GPIO_PuPd,GPIO_Label
PB13.GPIO_Label=ETH_CODE4
PB13.GPIO_PuPd=GPIO_PULLDOWN
PB13.Signal=GPIO_Input
PB14.GPIOParameters=GPIO_PuPd,GPIO_Label
PB14.GPIO_Label=ETH_CODE3
PB14.GPIO_PuPd=GPIO_PULLDOWN
PB14.Signal=GPIO_Input
PB15.GPIOParameters=GPIO_PuPd,GPIO_Label
PB15.GPIO_Label=ETH_CODE2
PB15.GPIO_PuPd=GPIO_PULLDOWN
PB15.Signal=GPIO_Input
PC1.Mode=RMII
PC1.Signal=ETH_MDC
PC10.Mode=Full_Duplex_Master
PC10.Signal=SPI3_SCK
PC11.Mode=Full_Duplex_Master
PC11.Signal=SPI3_MISO
PC12.Mode=Full_Duplex_Master
PC12.Signal=SPI3_MOSI
PC4.Mode=RMII
PC4.Signal=ETH_RXD0
PC5.Mode=RMII
PC5.Signal=ETH_RXD1
PD11.GPIOParameters=PinState,GPIO_Label
PD11.GPIO_Label=LED_RED
PD11.PinState=GPIO_PIN_SET
PD11.Signal=GPIO_Output
PD12.GPIOParameters=PinState,GPIO_Label
PD12.GPIO_Label=LED_GREEN
PD12.PinState=GPIO_PIN_SET
PD12.Signal=GPIO_Output
PD13.GPIOParameters=PinState,GPIO_Label
PD13.GPIO_Label=LED_BLUE
PD13.PinState=GPIO_PIN_SET
PD13.Signal=GPIO_Output
PD8.GPIOParameters=GPIO_PuPd,GPIO_Label
PD8.GPIO_Label=ETH_CODE1
PD8.GPIO_PuPd=GPIO_PULLDOWN
PD8.Signal=GPIO_Input
PD9.GPIOParameters=GPIO_PuPd,GPIO_Label
PD9.GPIO_Label=ETH_CODE0
PD9.GPIO_PuPd=GPIO_PULLDOWN
PD9.Signal=GPIO_Input
PE10.GPIOParameters=GPIO_Speed,PinState,GPIO_PuPd,GPIO_Label
PE10.GPIO_Label=RELAY2_nRST
PE10.GPIO_PuPd=GPIO_PULLUP
PE10.GPIO_Speed=GPIO_SPEED_FREQ_VERY_HIGH
PE10.PinState=GPIO_PIN_SET
PE10.Signal=GPIO_Output
PE11.GPIOParameters=GPIO_Speed,PinState,GPIO_PuPd,GPIO_Label
PE11.GPIO_Label=RELAY2_nCS0
PE11.GPIO_PuPd=GPIO_PULLUP
PE11.GPIO_Speed=GPIO_SPEED_FREQ_VERY_HIGH
PE11.PinState=GPIO_PIN_SET
PE11.Signal=GPIO_Output
PE12.GPIOParameters=GPIO_Speed,PinState,GPIO_PuPd,GPIO_Label
PE12.GPIO_Label=RELAY2_nCS1
PE12.GPIO_PuPd=GPIO_PULLUP
PE12.GPIO_Speed=GPIO_SPEED_FREQ_VERY_HIGH
PE12.PinState=GPIO_PIN_SET
PE12.Signal=GPIO_Output
PE13.GPIOParameters=GPIO_Speed,PinState,GPIO_Label
PE13.GPIO_Label=RELAY2_nCS2
PE13.GPIO_Speed=GPIO_SPEED_FREQ_VERY_HIGH
PE13.PinState=GPIO_PIN_SET
PE13.Signal=GPIO_Output
PE14.GPIOParameters=GPIO_Speed,PinState,GPIO_PuPd,GPIO_Label
PE14.GPIO_Label=RELAY2_nCS3
PE14.GPIO_PuPd=GPIO_PULLUP
PE14.GPIO_Speed=GPIO_SPEED_FREQ_VERY_HIGH
PE14.PinState=GPIO_PIN_SET
PE14.Signal=GPIO_Output
PE15.GPIOParameters=GPIO_Speed,PinState,GPIO_PuPd,GPIO_Label
PE15.GPIO_Label=RELAY2_nCS4
PE15.GPIO_PuPd=GPIO_PULLUP
PE15.GPIO_Speed=GPIO_SPEED_FREQ_VERY_HIGH
PE15.PinState=GPIO_PIN_SET
PE15.Signal=GPIO_Output
PE2.Mode=Full_Duplex_Master
PE2.Signal=SPI4_SCK
PE5.Mode=Full_Duplex_Master
PE5.Signal=SPI4_MISO
PE6.Mode=Full_Duplex_Master
PE6.Signal=SPI4_MOSI
PE7.GPIOParameters=GPIO_Speed,PinState,GPIO_PuPd,GPIO_Label
PE7.GPIO_Label=RELAY1_nCS1
PE7.GPIO_PuPd=GPIO_PULLUP
PE7.GPIO_Speed=GPIO_SPEED_FREQ_VERY_HIGH
PE7.PinState=GPIO_PIN_SET
PE7.Signal=GPIO_Output
PE8.GPIOParameters=GPIO_Speed,PinState,GPIO_PuPd,GPIO_Label
PE8.GPIO_Label=RELAY1_nCS0
PE8.GPIO_PuPd=GPIO_PULLUP
PE8.GPIO_Speed=GPIO_SPEED_FREQ_VERY_HIGH
PE8.PinState=GPIO_PIN_SET
PE8.Signal=GPIO_Output
PF13.GPIOParameters=GPIO_Speed,GPIO_PuPd,GPIO_Label
PF13.GPIO_Label=MCU_FLASH1_CS
PF13.GPIO_PuPd=GPIO_PULLUP
PF13.GPIO_Speed=GPIO_SPEED_FREQ_VERY_HIGH
PF13.Signal=GPIO_Output
PF14.GPIOParameters=GPIO_Speed,GPIO_PuPd,GPIO_Label
PF14.GPIO_Label=MCU_FLASH2_CS
PF14.GPIO_PuPd=GPIO_PULLUP
PF14.GPIO_Speed=GPIO_SPEED_FREQ_VERY_HIGH
PF14.Signal=GPIO_Output
PF15.GPIOParameters=GPIO_Speed,PinState,GPIO_PuPd,GPIO_Label
PF15.GPIO_Label=RELAY1_nCS4
PF15.GPIO_PuPd=GPIO_PULLUP
PF15.GPIO_Speed=GPIO_SPEED_FREQ_VERY_HIGH
PF15.PinState=GPIO_PIN_SET
PF15.Signal=GPIO_Output
PF7.Mode=Full_Duplex_Master
PF7.Signal=SPI5_SCK
PF8.Mode=Full_Duplex_Master
PF8.Signal=SPI5_MISO
PF9.Mode=Full_Duplex_Master
PF9.Signal=SPI5_MOSI
PG0.GPIOParameters=GPIO_Speed,PinState,GPIO_PuPd,GPIO_Label
PG0.GPIO_Label=RELAY1_nCS3
PG0.GPIO_PuPd=GPIO_PULLUP
PG0.GPIO_Speed=GPIO_SPEED_FREQ_VERY_HIGH
PG0.PinState=GPIO_PIN_SET
PG0.Signal=GPIO_Output
PG1.GPIOParameters=GPIO_Speed,PinState,GPIO_PuPd,GPIO_Label
PG1.GPIO_Label=RELAY1_nCS2
PG1.GPIO_PuPd=GPIO_PULLUP
PG1.GPIO_Speed=GPIO_SPEED_FREQ_VERY_HIGH
PG1.PinState=GPIO_PIN_SET
PG1.Signal=GPIO_Output
PG11.Mode=RMII
PG11.Signal=ETH_TX_EN
PG13.Mode=RMII
PG13.Signal=ETH_TXD0
PG14.Mode=RMII
PG14.Signal=ETH_TXD1
PH0/OSC_IN.Mode=HSE-External-Oscillator
PH0/OSC_IN.Signal=RCC_OSC_IN
PH1/OSC_OUT.Mode=HSE-External-Oscillator
PH1/OSC_OUT.Signal=RCC_OSC_OUT
RCC.HSE_VALUE=8000000
RCC.SYSCLKFreq_VALUE=216000000
RCC.SYSCLKSource=RCC_SYSCLKSOURCE_PLLCLK
board=custom
